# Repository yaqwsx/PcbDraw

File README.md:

# PcbDraw

Convert your KiCad boards into nice looking 2D drawings suitable for pinout
diagrams. Never draw them manually again!

This tool takes a KiCad board (.kicad_pcb file) and produces a 2D
nice looking drawing of the board as an SVG file. This allows you to quickly and
automatically create awesome pinout diagrams for your project. These diagrams
are much easier to read than a labeled photo of a physical board or an actual
KiCad design.

You and your users will love them!

PcbDraw also comes with a small utility called Populate which allows you to
easily specify & maintain nice looking HTML or Markdown population manuals.

And, also, as a bonus it allows you to programmatically obtain 3D-rendered
previews of your boards (e.g., in CI).

## Installation

PcbDraw supports **KiCad 9 and 10** and is distributed as a Python package
`pcbdraw`. It uses the stable `kicad-cli` interface and does not depend on
KiCad's Python `pcbnew` module. It also requires Inkscape 1 or librsvg installed.
Read more details in the [installation guide](doc/installation.md).

## Usage

There are two separate guides:

- [usage of PcbDraw](doc/pcbdraw.md)
- [usage of Populate](doc/populate.md)
- [library management tools](doc/library.md)
- [board annotations API](doc/annotations.md)

There are also examples of usage in the `examples` directory.

## PcbDraw seems to be broken!

Please, read [FAQ](doc/faq.md) first. If it does not answer your problem, feel
free to open issue on GitHub.

## Contributing

Feel free to submit issues and pull requests!

## Future Work

- make reasonably complete module library

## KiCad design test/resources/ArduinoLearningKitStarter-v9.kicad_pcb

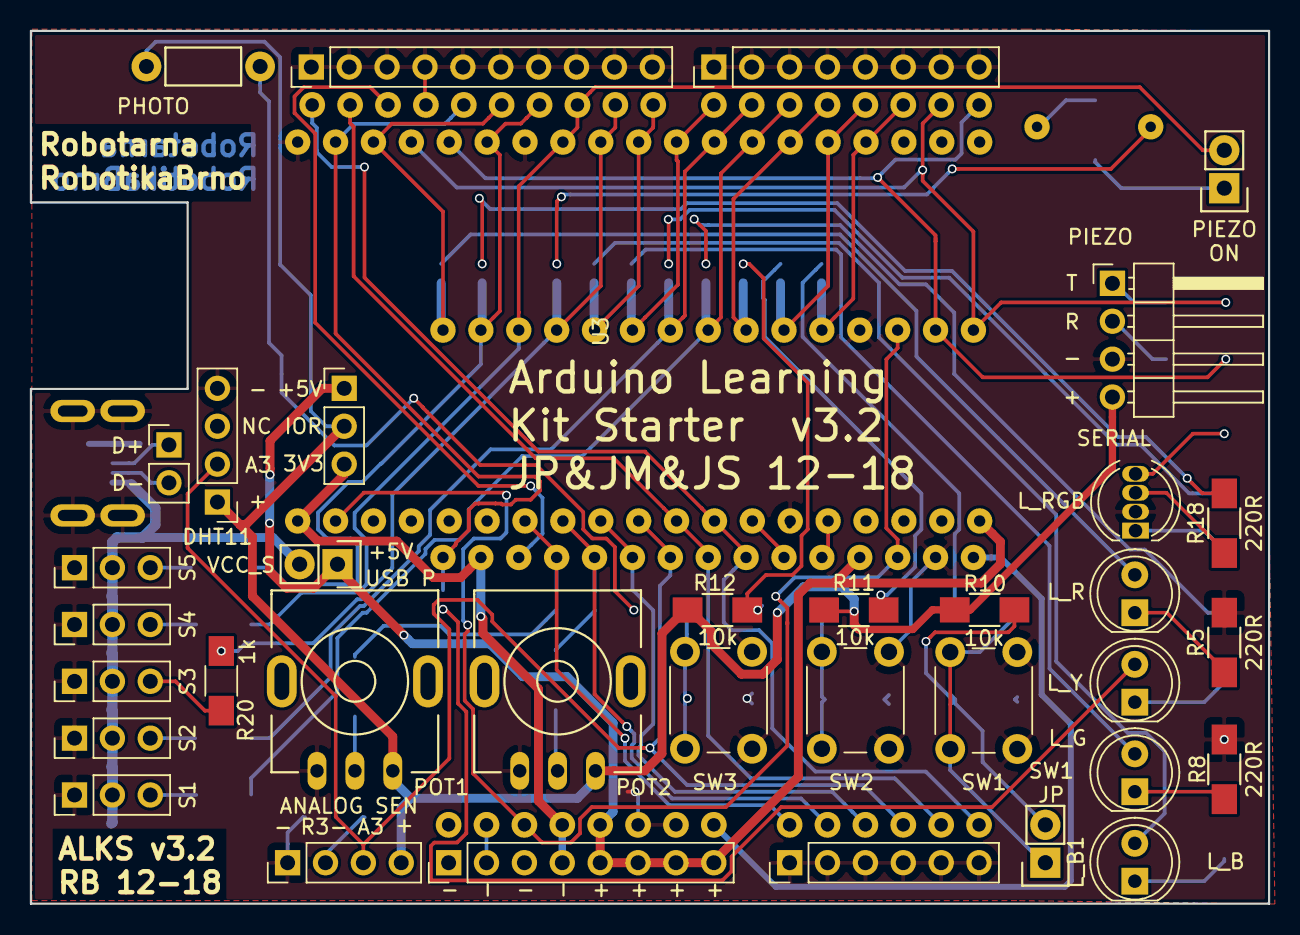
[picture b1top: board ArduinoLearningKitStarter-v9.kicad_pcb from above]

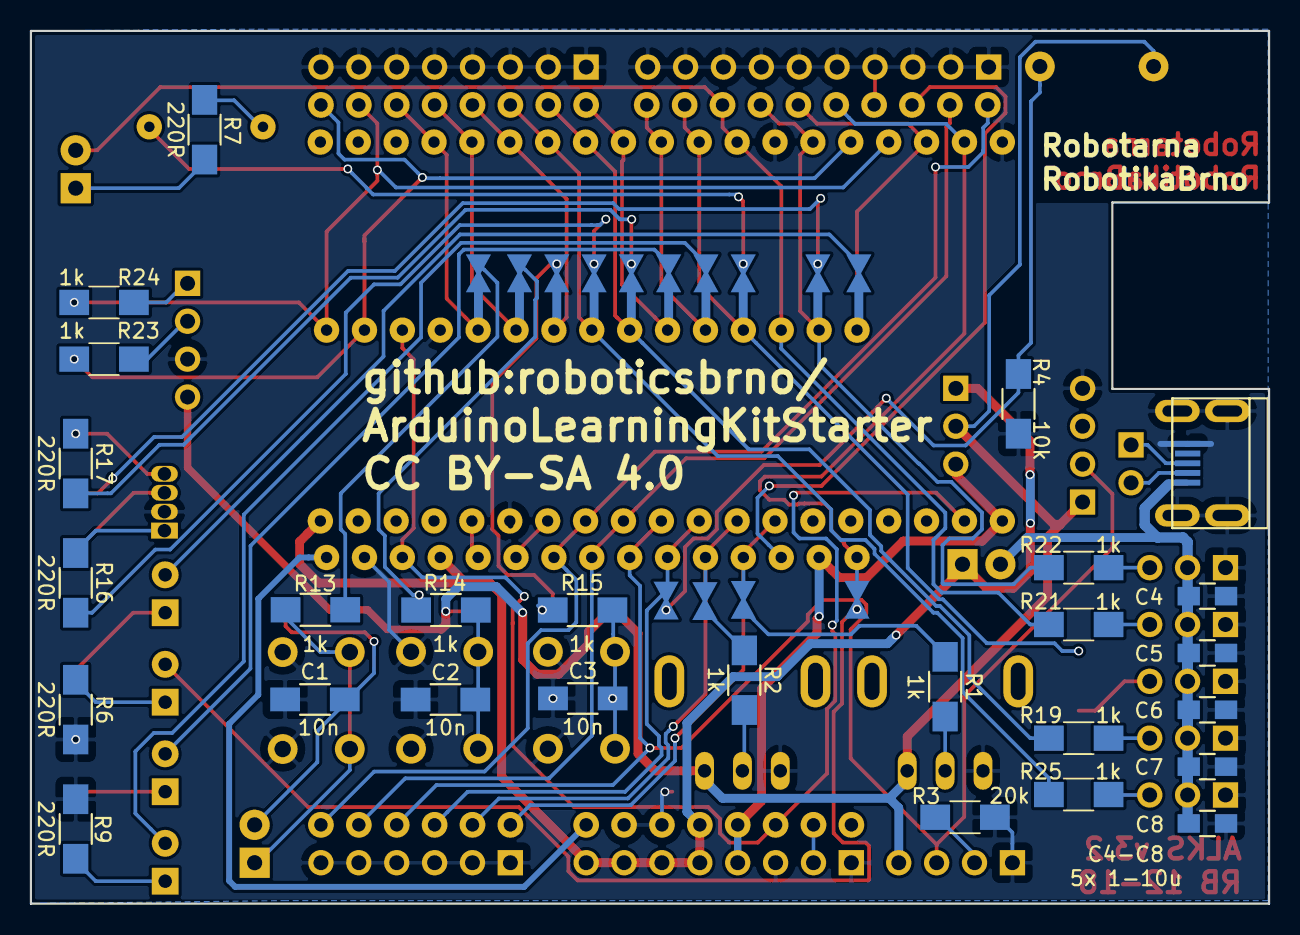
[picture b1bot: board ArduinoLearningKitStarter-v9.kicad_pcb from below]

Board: 2 copper layers, 83.0 x 58.5 mm, 80 parts (41 on the bottom side), 70 nets.

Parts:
C1, C2, C3: 10n; C_1206_HandSoldering
C4, C5, C7, C8: 10uF; C_0805_HandSoldering
C6: 10 μF; C_0805_HandSoldering
DHT11: DHT11_CONN; PinHeader_1x04_P2.54mm_Vertical
J1: USB_OTG; USB_Micro-B-widened
J2, J4: CONN_01X08; PinHeader_1x08_P2.54mm_Vertical
J3: CONN_01X06; PinHeader_1x06_P2.54mm_Vertical
J5: CONN_01X10; PinHeader_1x10_P2.54mm_Vertical
J6: CONN_01X04; PinHeader_1x04_P2.54mm_Horizontal
J7: CONN_01X04; PinHeader_1x04_P2.54mm_Vertical
J8: CONN_01X02; PinHeader_1x02_P2.54mm_Vertical
JP1, JP2, JP3, JP4, JP5, JP6, JP7, JP8, JP10, JP11, JP12, JP13, JP14, JP15: Jumper_NC_Small; CUT_BRIDGGE
JP9, JP16, JP17: Jumper; Pin_Header_Straight_1x02
JP18: Jumper_NC_Dual; PinHeader_1x03_P2.54mm_Vertical
L_B1: LED; LED_D5.0mm
L_G1: LED; LED_D5.0mm
L_R1: LED; LED_D5.0mm
L_RGB1: LED_RCBG; LED_D5.0mm-4_RGB
L_Y1: LED; LED_D5.0mm
PHOTO1: Photores; Resistor_Horizontal_RM7mm
PIEZO1: PIEZO; piezo_12
R1, R2, R13, R14, R15, R19, R20, R21, R22, R23, R24, R25: 1k; R_1206_HandSoldering
R3: 20k; R_1206_HandSoldering
R4, R10, R11, R12: 10k; R_1206_HandSoldering
R5, R6, R7, R8, R9, R16, R17, R18: 220R; R_1206_HandSoldering
RV1, RV2: 10k; RV09
S1: SERVO1; PinHeader_1x03_P2.54mm_Vertical
S2: SERVO2; PinHeader_1x03_P2.54mm_Vertical
S3: SERVO3; PinHeader_1x03_P2.54mm_Vertical
S4: SERVO4; PinHeader_1x03_P2.54mm_Vertical
S5: SERVO5; PinHeader_1x03_P2.54mm_Vertical
SW1, SW2, SW3: SW_PUSH; SW_PUSH_6mm
U1: arduino_nano
U2: arduino_uno; arduino_uno_small_pads
U3: ESP32-DEVKIT-C

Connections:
+3V3: J2.4, JP18.3, U1.2, U2.4, U3.1
+5V: J2.5, J2.6, J2.7, J2.8, JP9.1, JP18.1, U1.12, U2.5, U3.19
/D+: J1.3, J8.1
/D-: J1.2, J8.2
A0: JP2.1, U1.4, U2.9, U3.7
A1: JP3.1, U1.5, U2.10, U3.8
A2: JP1.1, U1.6, U2.11, U3.9
A3: DHT11.2, J7.3, U1.7, U2.12, U3.10
A4: U1.8, U2.13, U2.31, U3.11
A5: U1.9, U2.14, U2.32, U3.12
A6: U1.10, U3.13
A7: U1.11, U3.15
AREF: U1.3, U2.30
D0: R23.1, U1.17, U2.15, U3.34
D1: R24.1, U1.16, U2.16, U3.35
D2: JP10.1, U1.20, U2.17, U3.23
D3: JP11.1, U1.21, U2.18, U3.24
D4: JP12.1, U1.22, U2.19, U3.25
D5: JP13.2, R25.1, U1.23, U2.20, U3.26
D6: JP14.2, R19.1, U1.24, U2.21, U3.27
D7: JP7.1, U1.25, U2.22, U3.28
D8: JP8.1, U1.26, U2.23, U3.29
D9: JP4.1, R20.1, U1.27, U2.24, U3.30
D10: JP16.2, R21.1, U1.28, U2.25, U3.31
D11: JP15.2, R22.1, U1.29, U2.26, U3.33
D12: JP5.1, U1.30, U2.27, U3.36
D13: JP6.1, U1.1, U2.28, U3.37
GND: C1.1, C2.1, C3.1, C4.2, C5.2, C6.2, C7.2, C8.2, DHT11.4, J1.5, J1.6, J2.1, J2.3, J3.1, J3.2, J3.3, J3.4, J3.5, J3.6, J4.1, J4.2, J4.3, J4.4, J4.5, J4.6, J4.7, J4.8, J5.1, J5.2, J5.3, J5.4, J5.5, J5.6, J5.7, J5.8, J5.9, J5.10, J6.3, J7.1, L_RGB1.2, R3.1, R4.2, R5.1, R6.1, R8.1, R9.1, RV1.1, RV2.1, S1.1, S2.1, S3.1, S4.1, S5.1, SW1.2, SW2.2, SW3.2, U1.14, U1.19, U2.6, U2.7, U2.29, U3.14, U3.32, U3.38
IOREF: J2.2, U2.2
IOREF_U: DHT11.1, J6.4, J7.4, JP18.2, PHOTO1.1, R10.1, R11.1, R12.1, RV1.3, RV2.3
unnamed: C1.2, JP17.2, R10.2
unnamed: C2.2, R14.1, SW2.1
unnamed: C3.2, R15.1, SW3.1
unnamed: J6.1, R24.2
unnamed: J6.2, R23.2
unnamed: J7.2, R3.2
unnamed: JP1.2, PHOTO1.2, R4.1
unnamed: JP2.2, R1.2
unnamed: JP3.2, R2.2
unnamed: JP4.2, PIEZO1.2
unnamed: JP5.2, L_R1.2
unnamed: JP6.2, L_Y1.2
unnamed: JP7.2, L_G1.2
unnamed: JP8.2, L_B1.2
unnamed: JP10.2, R13.2
unnamed: JP11.2, R11.2, R14.2
unnamed: JP12.2, R12.2, R15.2
unnamed: JP13.1, R16.1
unnamed: JP14.1, R17.1
unnamed: JP15.1, R18.1
unnamed: JP16.1, R7.1
unnamed: JP17.1, R13.1, SW1.1
unnamed: L_B1.1, R9.2
unnamed: L_G1.1, R8.2
unnamed: L_R1.1, R5.2
unnamed: L_RGB1.1, R16.2
unnamed: L_RGB1.3, R18.2
unnamed: L_RGB1.4, R17.2
unnamed: L_Y1.1, R6.2
unnamed: PIEZO1.1, R7.2
unnamed: R1.1, RV1.2
unnamed: R2.1, RV2.2
unnamed: R19.2, S2.3
unnamed: R20.2, S3.3
unnamed: R21.2, S4.3
unnamed: R22.2, S5.3
unnamed: R25.2, S1.3
RST: U1.13, U1.18, U2.3, U3.2
VCC: U1.15, U2.8
VCC_SERVO: C4.1, C5.1, C6.1, C7.1, C8.1, J1.1, JP9.2, S1.2, S2.2, S3.2, S4.2, S5.2

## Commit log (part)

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2017-04-13 Initial release
2017-04-13 Fix unicode error and allow usage with nightly
2017-04-28 Add many module support as a comma separated list
2017-04-28 Add lookup rule comment in README.md
2017-05-04 Produce valid A element of path
    There were trailing floating point zeroes on argument, which were expected to be
    integers. Some viewers (inkscpae, google-chrome) did not render image correctly.
2017-05-04 Fix typo & style
2017-05-04 Use mask instead of clipping path for pads
2017-05-18 Check if SetPlotOutlineMode exists
2017-06-09 Make style argument optional
2018-02-24 Adapt to changes in nighlty KiCAD API
2018-05-18 Fix a typo in the generated SVG
2018-07-17 add the ability to render the back side of the board
2018-07-17 clean up
2018-07-17 update the documenatation
    adding the --back and --mirror flag
2018-07-18 Add the ability to render the back of a compoent
    you need to create a file with the same name and but with the extension
    ".back.svg" instead of the ".svg"
2018-07-25 Remove debug print
2018-07-30 Add support for component highlighting
2018-07-30 Add ids of board, highlight and component containers
2018-07-30 Remove completed future work from readme
2018-07-31 Take aruguments in a more intuitive order
2018-07-31 Implement markdown output in populate
2018-08-01 Add support for image conversion
2018-08-01 Relativize paths from source file
2018-08-01 Create deepcopy during markdown parsing to prevent unexpected behavior
2018-08-02 Add Populate to readme and doc
2018-08-02 Fix mismatch in Populate doc
2018-08-02 Make paths in PcbDraw arguments relative to the source file
2018-08-02 Add remapping to Populate examples
2018-08-03 Add examples for PcbDraw
2018-08-03 Remove old promo
2019-05-07 Extend support to python3 and add the missing style config to default style
2019-05-09 Convert back to bytes when using python3
2019-08-06 Migrate to Python3
2019-08-07 Prepare PcbDraw for pip packaging
2019-08-07 Add option to use pre-packed libraries
2019-09-03 Make PcbDraw back-compatible with Python 2 because of Windows
2020-04-08 Add option to render V-CUTS
2020-04-08 Bump version
2020-05-05 Use wand instead of cairo to get higher quality PNG images
2020-05-05 Clear old packages in Makefile
2020-06-30 Subtract soldermask from silkscreen
2020-06-30 Draw exposed substrate
2020-06-30 Properly print errors
2020-07-03 Checkout v3.1 of ArduinoLearningKitStarter
    The footprint library is designed to work with v3.1 of
    ArduinoLearningKitStarter.
    Also the aspect of the example is for this version.
    If the user uses a newer version will get the idea that the script doesn't
    work as expected.
2020-07-09 Add support for JPG output, deduce file type based on extension
2020-07-09 Handle non-file PcbDraw options in Populate
2020-07-09 Add support for builtin styles, add new styles
2020-07-09 Refactor library path
2020-07-09 Make warning about back side components optional.
    Messages about missing *.back component images are emitted only if the
    --warn-back command line option is specified.
2020-07-09 Look for styles and footprints also in /usr/share/pcbdraw/
    This decouples the scripts from their data.
    Data can be installed in GLOBAL_DATA_DIR (/usr/share/pcbdraw/)
    Footprints:
    - In addition to use PKG_BASE for default libs now we also look on
    GLOBAL_DATA_DIR
    Styles:
2020-07-10 Look for templates also in /usr/share/pcbdraw/
    This decouples the scripts from their data.
    Data can be installed in GLOBAL_DATA_DIR (/usr/share/pcbdraw/)
    Templates:
    - We try in the current directory.
    - Then we try to add '.handlebars' extension and look again.
    - Try in PKG_BASE
2020-07-10 Use yaml.safe_load instead of yaml.load
    There two reasons for this:
    - The Debian stable version of PyYAML doesn't have yaml.FullLoader
    - I think is better to use the safe version for a configuration file.
    We are not using YAML for persistence.
2020-07-10 Fix jlcpcb* styles
    The enig and hasl styles were swapped.
2020-07-10 Removed image extension debug message.
    I suggest adding a logging.debug functionality.
    I'm using: https://github.com/INTI-CMNB/kiplot/blob/master/kiplot/log.py
2020-07-10 Fix warnings about extra keys in styles.
    vcut and highlight-padding are required keys.
2020-07-13 Change --war-back to --no-warn-back to print the warnings by default.
2020-07-14 Avoid failing in the calls to sysconfig.get_path
    Also default to no scheme.
2020-07-19 Tidy up dependencies
    - argparse is no longer needed for Python3
    - pyaml is too complex, pyyaml is sufficient
2020-07-21 Small updates to the docs.
2020-07-21 Added the search path to the help.
2020-07-21 Dcoumented the search path.
2020-07-30 Update pcbdraw.md
    Flip order to match argument list
2020-08-05 Fix typo in SVG causing opaque holes
2020-08-05 Move versioneer to setup requirements
2020-08-25 Fixed problems when running pcbdraw without installing.
2020-09-04 Added two strategies to compute the real bounding box.
    * -r, --remove-hidden Remove board drawings in hidden layers
    Removes all drawings in user and fab layers.
    These drawings aren't included in the SVG and only bloat the BBox.
    * -e, --adjust-to-edge Adjust size to the board edge
    Asks pcbnew to use the board edge to compute the BBox.
    The second is perfect for the board without components, but coul crop
2020-10-27 Bump library version
2020-10-27 Fix remapping of component back sides
2021-01-10 Fix clean build of package
2021-03-03 Fix drawing PCBs without modules
    Drawing PCB without modules (for example edges only) were causing crash
    due to module variable not being None (empty list). Using
    pcbnew.MODULE_List.GetFirst() before iterating through elements seems to
    be fixing this issue.
2021-05-03 Fix drawing board polygon when the board is only a circle
2021-05-21 Use SVG units properly
2021-05-21 Implement shrinking support
2021-05-21 Add information about breaking change
2021-05-27 Fix misleading error
2021-05-28 Introduce compatibility with KiCAD nightly
2021-05-29 Optimize SVG - do not duplicate components and skip empty tags
2021-05-29 Add FAQ
2021-12-05 Fix various typos
    Found via `codespell -q 3`
2021-12-12 Fix shrinking for bitmaps
2021-12-17 Fixed issue with ComputeBoundingBox
2021-12-27 Specify pcbnewTransition dependency precisely
2021-12-28 Removed click as dependency, not really used.
2022-01-02 fixes #83 permission denied on windows 10
2022-01-30 Add via-rendering workaround
2022-03-01 Flipped 2 colors
2022-03-01 Preliminary feature addition for resistor color code
2022-03-01 Changes based off comments
2022-03-01 Added flip option and tollerance parsing
2022-03-01 Revert "Minor docs change"
    This reverts commit 9dca644c8c61010ca4c38128b2d633a9e5bb712b.
2022-03-01 Revert "Revert "Minor docs change""
    This reverts commit 503e26bbf096b8dcda67257ed5202b3e47b9267e.
2022-03-01 Add support for THT Resistor Color Code Markings
2022-03-03 Start custom SVG conversion module
2022-03-03 Improve error message when Inkscape is not availabe
2022-03-04 Update installation instructions
2022-03-04 Improve error reporting for RSVG
2022-03-04 Enable Inkscape strategy for Unix systems
2022-03-11 Start a module for 3D renderings
2022-03-14 Fix missing import
2022-03-14 Include resources in the final package
2022-03-15 fixup! DBG: Add debug prints
2022-03-15 fixup! fixup! DBG: Add debug prints
2022-03-15 Change waiting strategy
2022-03-15 Fix broken remapping
2022-03-17 Fix outline rendering
2022-03-25 Try supressing KiCAD locale warnings
2022-03-25 Migrate resource into a coommon subdirectory
2022-03-26 Fixed coloring and resistor_values code
2022-03-26 Fix loading styles
2022-03-26 Setup base of automated testing
2022-03-28 Simplify test assertions
2022-03-29 Improve reliability of renderer
2022-05-25 Do not plot drill marks
2022-06-08 Typo
2022-06-08 Fix remapping components on the back side
    Before, a remapped component would show its front graphic on both sides
    of the PCB.
2022-06-08 Fix highlight position for SVGs with nonzero viewbox origin
2022-06-26 Increase outline tolerance
2022-07-29 Bump mistune from 0.8.4 to 2.0.3
    Bumps [mistune](https://github.com/lepture/mistune) from 0.8.4 to 2.0.3.
    - [Release notes](https://github.com/lepture/mistune/releases)
    - [Changelog](https://github.com/lepture/mistune/blob/master/docs/changes.rst)
    - [Commits](https://github.com/lepture/mistune/compare/v0.8.4...v2.0.3)
    ---
    updated-dependencies:
2022-08-30 Fix Kicad 6.99 compatibility issues
2022-09-11 Add type annotations to populate
2022-09-22 Remove engineering number dependency
2022-09-22 Reorganize tests
2022-09-22 Rework outline reconstruciton to be reliable
2022-09-22 Resolve type annotation of renderer
2022-09-22 Implement support for initial components
2022-09-22 Handle properly when there ano default components
2022-09-22 Update promo
2022-09-29 Adds support for numpy<1.20
    - The numpy.typing was introduced in 1.20.
    - Current Debian stable uses 1.19.
    - The numpy.typing functionality is currently needed only for tests
    (mypy), not for runtime
2022-09-29 Fix executable permissions for pcbdraw/*.py scripts
    - plot.py can't be executed anymore
    - ui.py can be executed
2022-09-30 Fixes the default value for --libs
    - Currently footprints contain `KiCAD-base` not `KiCAD-6`
2022-10-05 Add 6.0.8 work-around for plotting layers
2022-10-05 Do not strictly depend on numpy.typing
2022-10-05 Fix typo in tests
2022-10-11 Recover mistune 0.8.4 support.
    - mistune 2.x is incompatible with 0.8.4
    - Debian stable uses 0.8.4, so installing 2.x at system level breaks
    all applications using mistune.
    - The patch is small and the important code is shared between the two
    versions.
2022-10-11 Fixed and improved the read_resistance function for better resistance handling. Fixes #117
2022-10-12 Default behavior for pcbdraw without subcommand
    - This makes the command line compatible with v0.9.0
2022-10-24 Preserve v5 support
2022-11-07 Do not use pyvirtual display on Windows
2023-01-11 Relax pcbnewTransition dependencies
2023-01-11 Preserve v5 compatibility
2023-02-23 Adapt to v7 release changes
2023-02-26 Bump lib
2023-05-20 Allow component rotation to be overridden in CLI
2023-05-21 add rotation to highlights
2023-07-25 Solving issue #152 - crash with "1 k" value resistor -> Nice message when "get_style" function does not work as expected.
2023-07-25 remove crash for value of 1 Ohm and below : TypeError: unsupported operand type(s) for /: 'decimal.Decimal' and 'float' Add value for multiplier of 0.1 Ohm and 0.01 Ohm
2023-11-05 Always reset cannonical orientation
2023-11-05 Update faking KiCAD environment
2023-11-05 Fix detecting drawing box
2023-12-29 Improvements to res coloring, added feature for 5 band and tolerance property
2024-01-01 Fixed resistor band values set, and updated for latest model Moved around resistor tolerance values, added 0.01% and 0.02% Fix bug where a value of `R` alone would count as 0 ohms Fixed lxml to ==4.9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
2024-01-08 Renamed variable to make mypy happy
2024-01-24 Moved feature over to ui.py, allowing not just populate to benefit
2024-03-24 Add `isV8()` to `LEGACY_KICAD` detection
    Solves https://github.com/yaqwsx/PcbDraw/issues/163
2024-03-24 Add missing double quote to DOCTYPE property
    This fixes an XML parser error with lxml 5.1.0
2024-03-25 Bump pcbnewTransition
2024-04-07 Updated comma list's regex to only have one or more word-only prefix
2024-04-18 get_closest optimization: - Try to find a perfect match - If not found look for the smaller distance - Avoid using power operation for the pseudo-distance
2024-04-29 Add deprecated methods fallback
2025-09-21 Get it installing and passing with Python 3.13 and KiCad 9
    I haven't verified that everything works beyond that it installs and
    `make test-unit test-system` passes.
2026-04-07 Add preliminary support for KiCAD v10
2026-04-07 Optimize substrate reconstruction
2026-04-07 Ensure we can read huge boards
2026-04-12 Fix transparency
2026-04-12 Bump footprints submodule

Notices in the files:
test/resources/ArduinoLearningKitStarter-v9.kicad_pcb:
CC BY-SA 4.0
